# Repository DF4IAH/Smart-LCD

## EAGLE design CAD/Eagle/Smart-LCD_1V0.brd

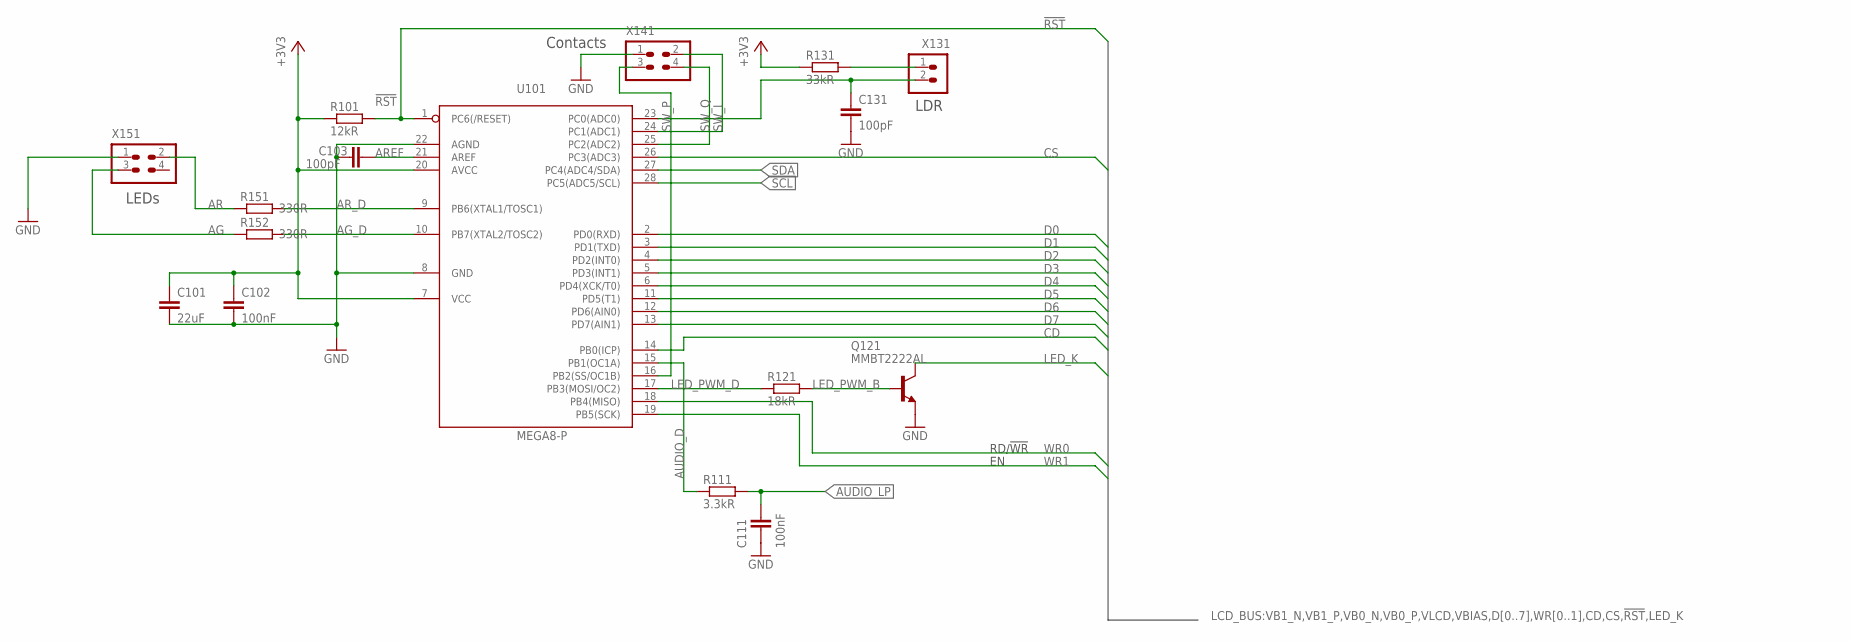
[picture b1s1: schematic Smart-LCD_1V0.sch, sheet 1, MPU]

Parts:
C101: 22uF; C0805
C102, C111: 100nF; C0805
C103, C131: 100pF; C0805
Q121: MMBT2222AL; SOT23
R101: 12kR; R0805
R111: 3.3kR; R0805
R121: 18kR; R0805
R131: 33kR; R0805
R151, R152: 330R; R0805
U101: MEGA8-P; DIL28-3
X131: LDR; 1X02
X141: Switches; 2X02
X151: LEDs; 2X02

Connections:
!RST: R101.2, U101.1 (PC6(/RESET)); also elsewhere on the board
+3V3: C101.1, C102.1, R101.1, R131.1, U101.7 (VCC), U101.20 (AVCC); also elsewhere on the board
AG: R152.1, X151.3
AG_D: R152.2, U101.10 (PB7(XTAL2/TOSC2))
AR: R151.1, X151.2
AREF: C103.2, U101.21 (AREF)
AR_D: R151.2, U101.9 (PB6(XTAL1/TOSC1))
AUDIO_D: R111.1, U101.15 (PB1(OC1A))
AUDIO_LP: C111.1, R111.2; also elsewhere on the board
CD: U101.14 (PB0(ICP)); also elsewhere on the board
CS: U101.26 (PC3(ADC3)); also elsewhere on the board
D0: U101.2 (PD0(RXD)); also elsewhere on the board
D1: U101.3 (PD1(TXD)); also elsewhere on the board
D2: U101.4 (PD2(INT0)); also elsewhere on the board
D3: U101.5 (PD3(INT1)); also elsewhere on the board
D4: U101.6 (PD4(XCK/T0)); also elsewhere on the board
D5: U101.11 (PD5(T1)); also elsewhere on the board
D6: U101.12 (PD6(AIN0)); also elsewhere on the board
D7: U101.13 (PD7(AIN1)); also elsewhere on the board
GND: C101.2, C102.2, C103.1, C111.2, C131.2, Q121.2 (E), U101.8 (GND), U101.22 (AGND), X141.1, X151.1; also elsewhere on the board
LDR: C131.1, U101.23 (PC0(ADC0)), X131.2
LDR_P: R131.2, X131.1
LED_K: Q121.3 (C); also elsewhere on the board
LED_PWM_B: Q121.1 (B), R121.2
LED_PWM_D: R121.1, U101.17 (PB3(MOSI/OC2))
SCL: U101.28 (PC5(ADC5/SCL)); also elsewhere on the board
SDA: U101.27 (PC4(ADC4/SDA)); also elsewhere on the board
SW_I: U101.24 (PC1(ADC1)), X141.2
SW_P: U101.16 (PB2(SS/OC1B)), X141.3
SW_Q: U101.25 (PC2(ADC2)), X141.4
WR0: U101.18 (PB4(MISO)); also elsewhere on the board
WR1: U101.19 (PB5(SCK)); also elsewhere on the board

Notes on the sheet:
LDR
Contacts
LEDs
RD/!WR

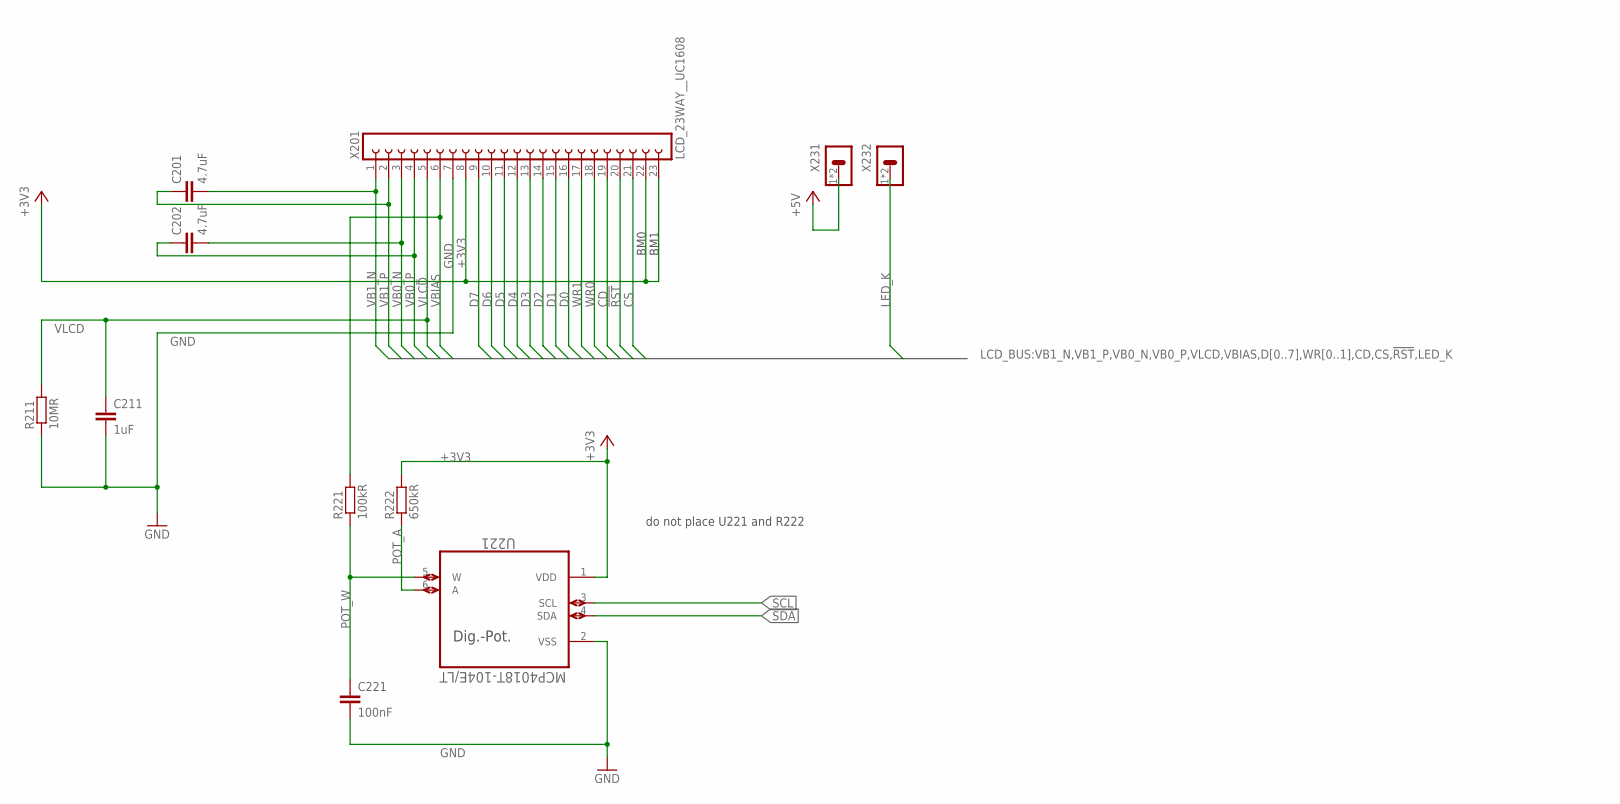
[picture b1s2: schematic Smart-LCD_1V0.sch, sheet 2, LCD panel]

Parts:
C201, C202: 4.7uF; C0805
C211: 1uF; C0805
C221: 100nF; C0805
R211: 10MR; R0805
R221: 100kR; R0805
R222: 650kR; R0805
U221: MCP4018T-104E/LT; SOT65P210X110-6N
X201: LCD_23WAY__UC1608; 23X01_1MM27__UC1608
X231: LED_A; P1-20X0.80
X232: LED_K; P1-20X0.80

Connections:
!RST: X201.20; also elsewhere on the board
+3V3: R222.2, U221.1 (VDD), X201.8, X201.22, X201.23; also elsewhere on the board
+5V: X231.1, X231.2; also elsewhere on the board
CD: X201.19; also elsewhere on the board
CS: X201.21; also elsewhere on the board
D0: X201.16; also elsewhere on the board
D1: X201.15; also elsewhere on the board
D2: X201.14; also elsewhere on the board
D3: X201.13; also elsewhere on the board
D4: X201.12; also elsewhere on the board
D5: X201.11; also elsewhere on the board
D6: X201.10; also elsewhere on the board
D7: X201.9; also elsewhere on the board
GND: C211.2, C221.2, R211.1, U221.2 (VSS), X201.7; also elsewhere on the board
LED_K: X232.1, X232.2; also elsewhere on the board
POT_A: R222.1, U221.6 (A)
POT_W: C221.1, R221.1, U221.5 (W)
SCL: U221.3 (SCL); also elsewhere on the board
SDA: U221.4 (SDA); also elsewhere on the board
VB0_N: C202.2, X201.3
VB0_P: C202.1, X201.4
VB1_N: C201.2, X201.1
VB1_P: C201.1, X201.2
VBIAS: R221.2, X201.6
VLCD: C211.1, R211.2, X201.5
WR0: X201.18; also elsewhere on the board
WR1: X201.17; also elsewhere on the board

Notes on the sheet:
Dig.-Pot.
BM1
BM0
do not place U221 and R222

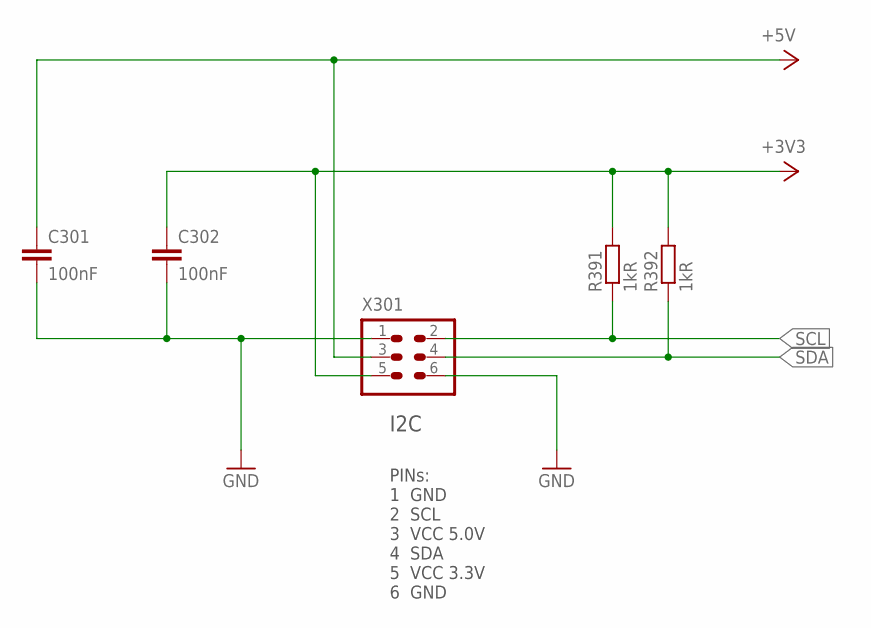
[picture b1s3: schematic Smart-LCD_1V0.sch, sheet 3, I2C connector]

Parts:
C301, C302: 100nF; C0805
R391, R392: 1kR; R0603
X301: I2C; 2X03

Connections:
+3V3: C302.1, R391.2, R392.2, X301.5; also elsewhere on the board
+5V: C301.1, X301.3; also elsewhere on the board
GND: C301.2, C302.2, X301.1, X301.6; also elsewhere on the board
SCL: R391.1, X301.2; also elsewhere on the board
SDA: R392.1, X301.4; also elsewhere on the board

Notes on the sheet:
I2C
PINs: 1 GND 2 SCL 3 VCC 5.0V 4 SDA 5 VCC 3.3V 6 GND

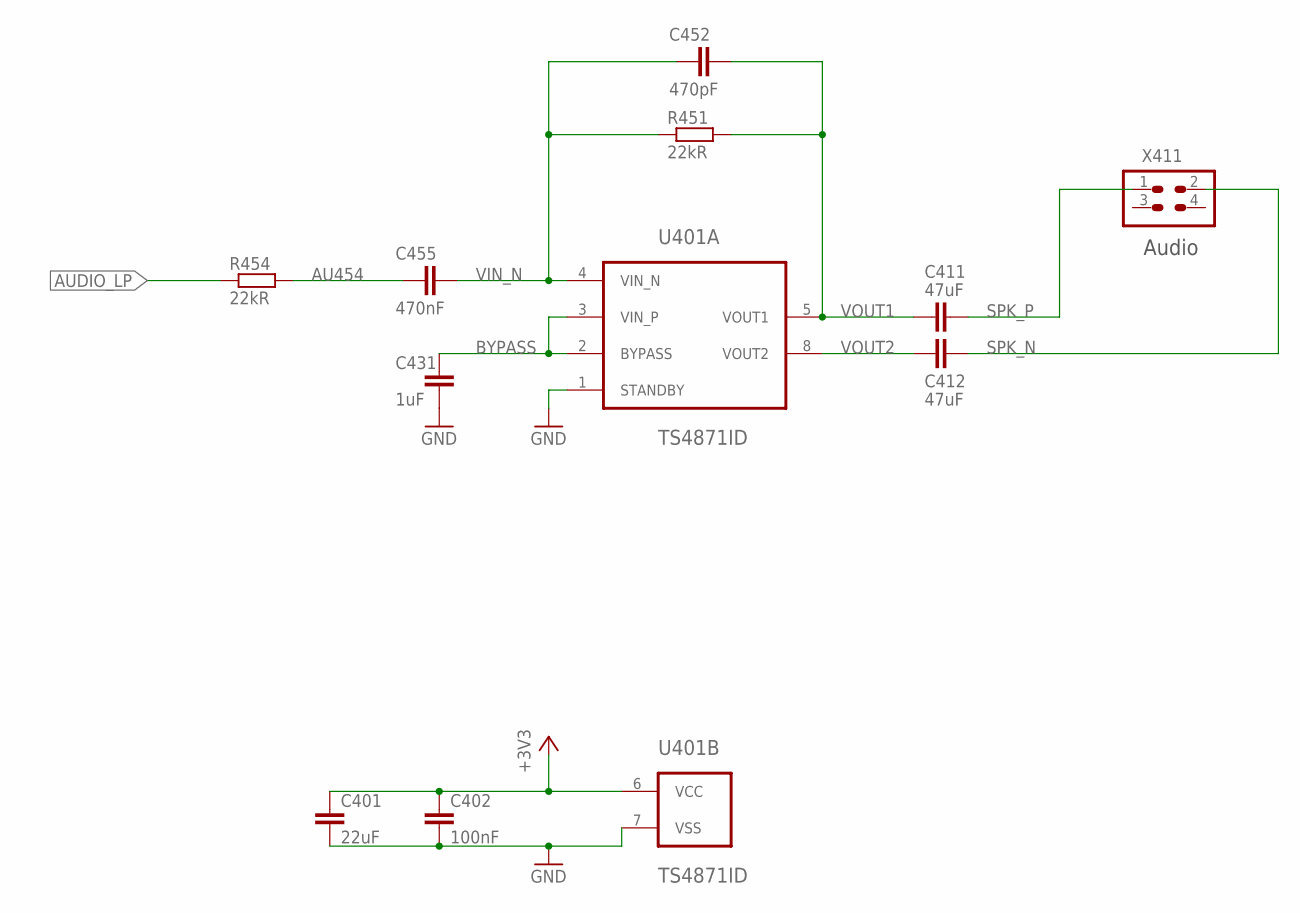
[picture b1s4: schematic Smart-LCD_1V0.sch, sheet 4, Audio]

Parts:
C401: 22uF; C0805
C402: 100nF; C0805
C411, C412: 47uF; C0805
C431: 1uF; C0805
C452: 470pF; C0805
C455: 470nF; C0805
R451, R454: 22kR; R0805
U401: TS4871ID; SO08
X411: Audio; 2X02

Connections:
+3V3: C401.1, C402.1, U401.6 (VCC); also elsewhere on the board
AU454: C455.1, R454.2
AUDIO_LP: R454.1; also elsewhere on the board
BYPASS: C431.1, U401.2 (BYPASS), U401.3 (VIN_P)
GND: C401.2, C402.2, C431.2, U401.1 (STANDBY), U401.7 (VSS); also elsewhere on the board
SPK_N: C412.2, X411.2
SPK_P: C411.2, X411.1
VIN_N: C452.1, C455.2, R451.1, U401.4 (VIN_N)
VOUT1: C411.1, C452.2, R451.2, U401.5 (VOUT1)
VOUT2: C412.1, U401.8 (VOUT2)

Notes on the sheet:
Audio

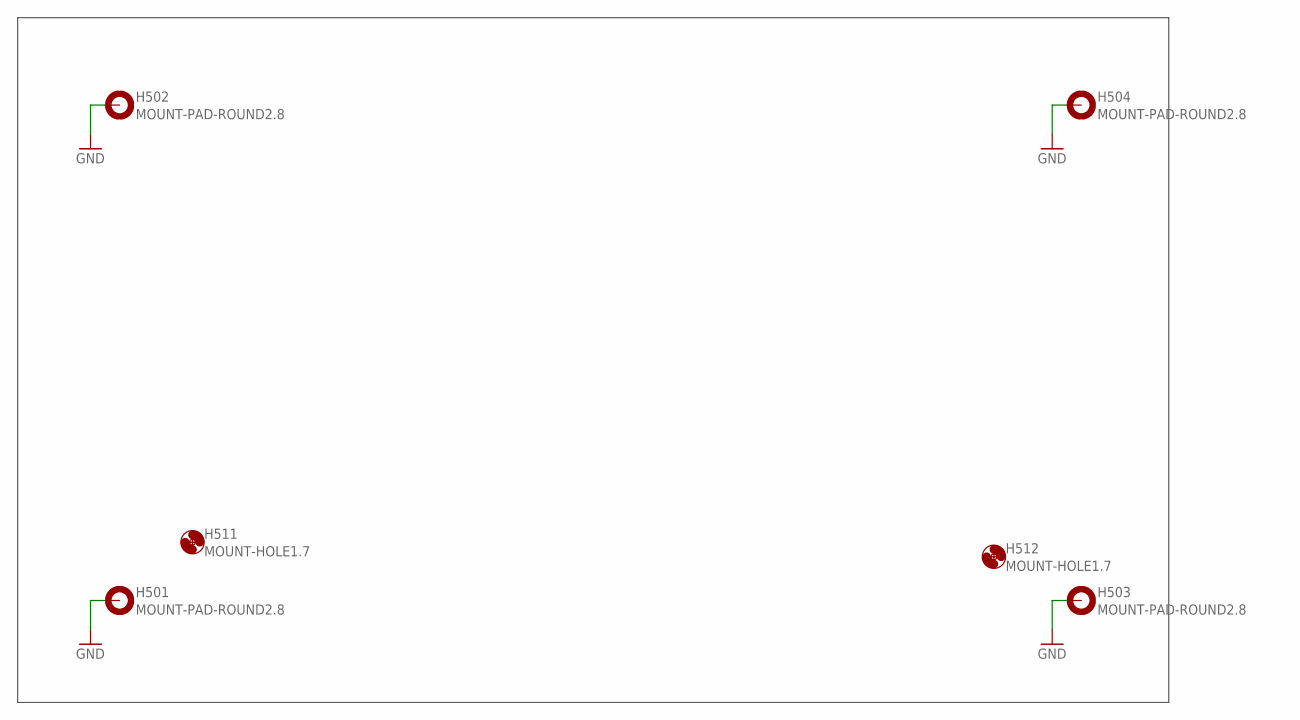
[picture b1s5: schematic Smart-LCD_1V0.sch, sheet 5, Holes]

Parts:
H501, H502, H503, H504: MOUNT-PAD-ROUND2.8; 2,8-PAD
H511, H512: MOUNT-HOLE1.7; 1,7

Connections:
GND: H501.B2,8, H502.B2,8, H503.B2,8, H504.B2,8; also elsewhere on the board

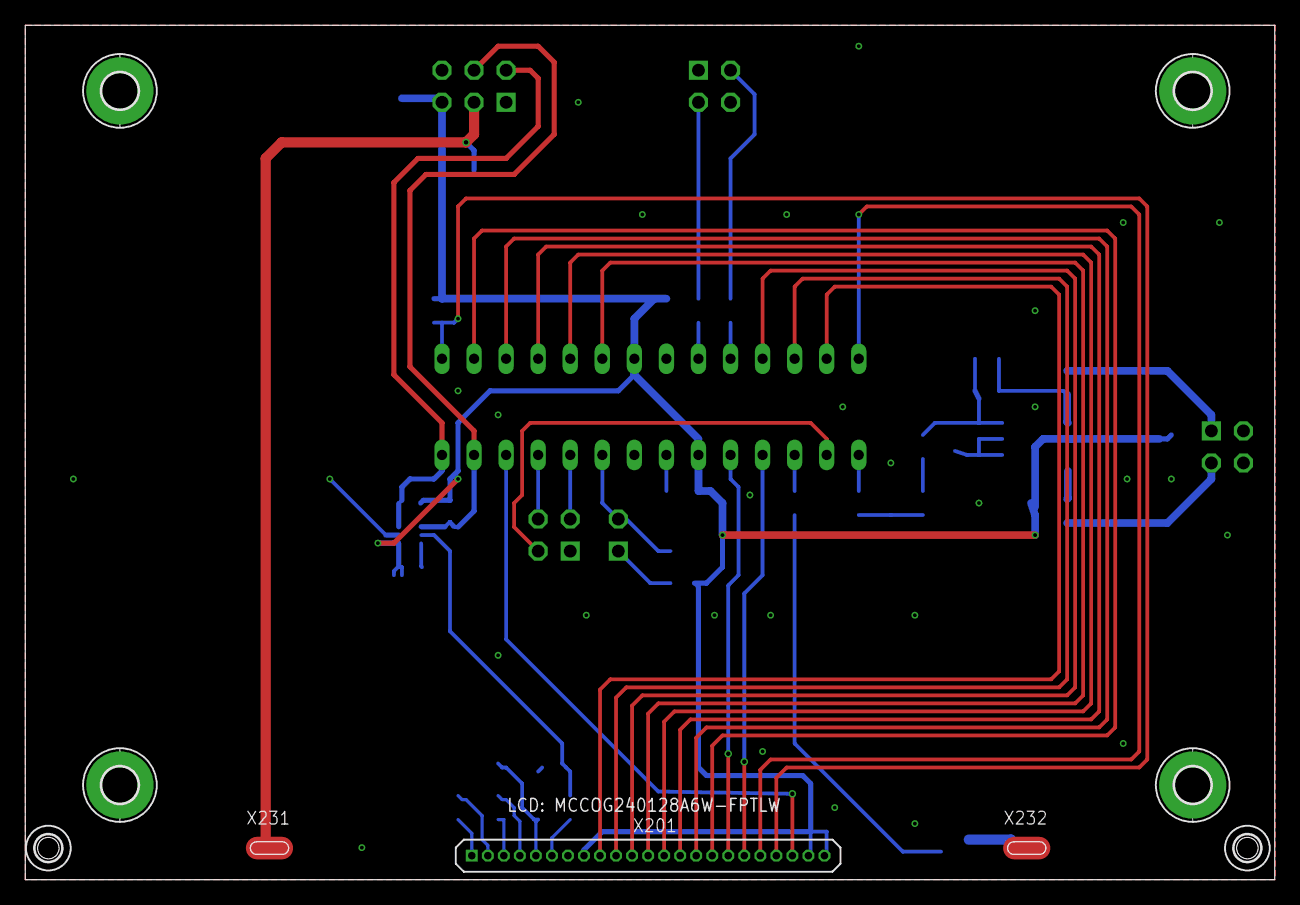
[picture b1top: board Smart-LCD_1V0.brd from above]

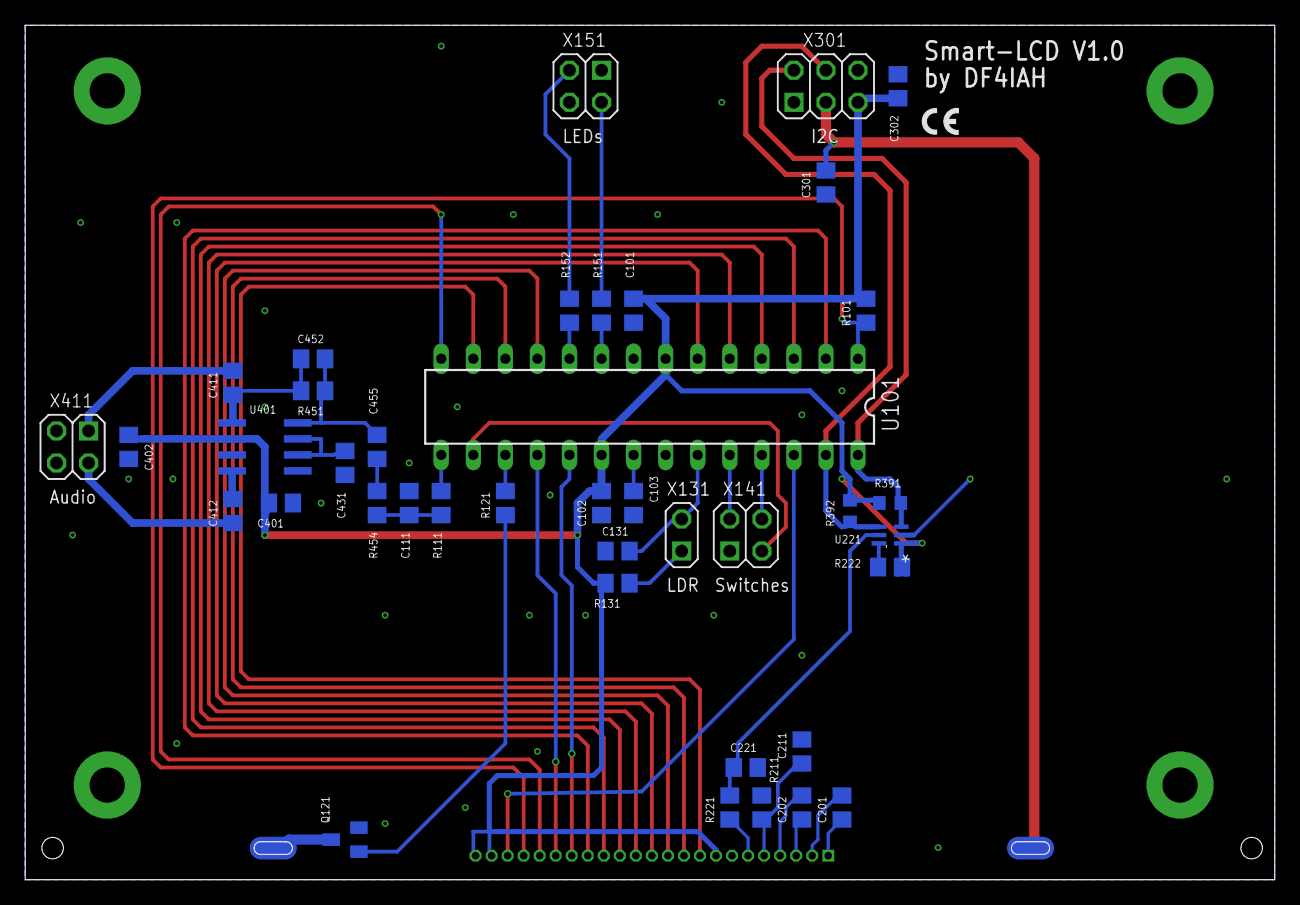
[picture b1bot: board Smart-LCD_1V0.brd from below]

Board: 2 copper layers, 99.0 x 67.7 mm, 49 parts (40 on the bottom side), 48 nets.

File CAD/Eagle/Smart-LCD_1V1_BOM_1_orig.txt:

Stückliste exportiert aus /Users/espero/Documents/eagle/Smart-LCD/Smart-LCD_1V1.sch am 30.05.17 14:22

Qty Value              Device             Package             Parts                              Description                            
1   100kR              R-EU_R0805         R0805               R221                               RESISTOR, European symbol              
6   100nF              C-EUC0805          C0805               C102, C111, C221, C301, C302, C402 CAPACITOR, European symbol             
2   100pF              C-EUC0805          C0805               C103, C131                         CAPACITOR, European symbol             
1   10MR               R-EU_R0805         R0805               R211                               RESISTOR, European symbol              
1   12kR               R-EU_R0805         R0805               R101                               RESISTOR, European symbol              
1   1MR                R-EU_R0805         R0805               R132                               RESISTOR, European symbol              
2   1kR                R-EU_R0805         R0805               R391, R392                         RESISTOR, European symbol              
2   1uF                C-EUC0805          C0805               C211, C431                         CAPACITOR, European symbol             
2   22kR               R-EU_R0805         R0805               R451, R454                         RESISTOR, European symbol              
2   22uF               C-EUC0805          C0805               C101, C401                         CAPACITOR, European symbol             
1   27R                R-EU_R0805         R0805               R131                               RESISTOR, European symbol              
1   3.3kR              R-EU_R0805         R0805               R111                               RESISTOR, European symbol              
2   330R               R-EU_R0805         R0805               R151, R152                         RESISTOR, European symbol              
1   4.7kR              R-EU_R0805         R0805               R121                               RESISTOR, European symbol              
2   4.7uF              C-EUC0805          C0805               C201, C202                         CAPACITOR, European symbol             
1   470nF              C-EUC0805          C0805               C455                               CAPACITOR, European symbol             
1   470pF              C-EUC0805          C0805               C452                               CAPACITOR, European symbol             
2   47uF               C-EUC0805          C0805               C411, C412                         CAPACITOR, European symbol             
1   650kR              R-EU_R0805         R0805               R222                               RESISTOR, European symbol              
1   Audio              HEADER-2X2         2X02                X411                               Header 2X2 2.54mm                      
1   BZX84-C2V4         BAS70-04           SOT23               D131                               Silicon Schottky Diodes                
4   FIDUCIAL_MARK_1MM  FIDUCIAL_MARK_1MM  FIDUCIAL_MARK_1MM   FM501, FM502, FM503, FM504         Fiducial Mark                          
1   I2C                HEADER-2X3         2X03                X301                               Header 2X3 2.54mm                      
1   LCD_23WAY__UC1608  LCD_23WAY__UC1608  23X01_1MM27__UC1608 X201                               Gfx-LCD UC1608 socket                  
1   LDR                HEADER-1X2         1X02                X131                               Header 1X2 2.54mm                      
1   LED_A              CON_1X             P1-20X0.80          X231                               THT contact 2mm x 0.80mm               
1   LED_K              CON_1X             P1-20X0.80          X232                               THT contact 2mm x 0.80mm               
1   LEDs               HEADER-2X2         2X02                X151                               Header 2X2 2.54mm                      
1   MCP4018T-104E/LT   MCP4018T-104E/LT   SOT65P210X110-6N    U221                               Digital POT                            
1   MEGA8-P            MEGA8-P            DIL28-3             U101                               MICROCONTROLLER                        
1   MMBT2222AL         MMBT2222AL         SOT23               Q121                               MMBT2222L, MMBT2222AL, SMMBT2222AL     
2   MOUNT-HOLE1.7      MOUNT-HOLE1.7      1,7                 H511, H512                         MOUNTING HOLE with drill center marker 
4   MOUNT-PAD-ROUND2.8 MOUNT-PAD-ROUND2.8 2,8-PAD             H501, H502, H503, H504             MOUNTING PAD, round                    
1   Switches           HEADER-2X2         2X02                X141                               Header 2X2 2.54mm                      
1   TS4871ID           TS4871ID           SO08                U401                               STMICROELECTRONICS  TS4871ID

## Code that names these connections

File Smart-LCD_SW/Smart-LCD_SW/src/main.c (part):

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	 * most critical pins are handled first.
	 */

	PORTB = 0b00010100;												// PB0: LCD-CD out-LO, PB1: AUDIO out (OC1A), PB2: SW_P in-PU, PB3: LCDBL out-AF-OC2A,
	DDRB  = 0b11111011;												// PB4: LCD-R/!W out-HI, PB5: LCD-EN out-LO, PB6: LEDRD out-LO, LEDGN out-LO

	PORTC = 0b01111110;												// PC0: LDR-ADC in-NoPU, PC1: SW_I in-PU, PC2: SW_Q in-PU, PC3: LCD-CS out-HI
	DDRC  = 0b00001000;												// PC4: I2C-SDA in-PU-AF-TWI, PC5: I2C-SCL in-PU-AF-TWI, PC6: RESET in-PU, PC7: -

	PORTD = 0xff;													// PD0..PD7: LCD-D0..LCD-D7 in-PU
	DDRD  = 0x00;

	// Analog input: Digital Disable Register
	DIDR0 = 0b00000001;												// PC0: LDR-ADC
}

static void s_tc_init(void)
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
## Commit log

2017-01-24 CAD, Docs - initial set-up
2017-01-24 SW - initial set-up
2017-02-03 CAD/Docs - initial set-up for new design
2017-02-04 CAD - first layout worked on
2017-02-04 Docs - BJT added
2017-02-04 Docs - ATmega328P added
2017-02-05 CAD - routed, but audio amplifier still TODO
2017-02-06 CAD - audio amplifier added, but CPU must be placed on the solder side
2017-02-06 CAD - CPU placed on the solder side
2017-02-07 CAD - minor corrections and PCB V1.0 ordering done
2017-02-08 SW - initial set-up with AVR-studio
2017-02-08 SW - ASF included
2017-02-08 SW - top-level main.c removed and ASF minimal code compiled
2017-02-08 SW - all needed ASF services and drivers added
2017-02-08 SW - I/O wires connected
2017-02-08 SW - some tests with the vector table done
2017-02-10 SW - TC0/1/2 init done
2017-02-11 SW - ADC init done, ISR: ADC done
2017-02-12 SW - sleep added, some more init and disable code added
2017-02-12 SW - SEI and CLI changed
2017-02-13 SW - ISR routines moved to isr.c|h module
2017-02-13 SW - TWI init added
2017-02-13 SW - TWI shutdown added
2017-02-13 SW - TWI state-machine added
2017-02-21 SW - TWI state-machine completed, TX double buffering added
2017-02-23 SW - LCD module added, additional sources for gfx_mono handling included
2017-02-23 SW - gfx_mono - hooks for LCD UC1608 added
2017-02-23 SW - gfx_mono - communication with UC1608 LCD implemented
2017-02-26 SW - display attached to new arrived PCB, some changes done at the LCD communication section
2017-02-26 SW - most of the display works, still searching for timer bug
2017-02-27 SW - timers are running, ADC ISR only one time called
2017-02-27 SW - ADC temperature working
2017-02-27 SW - test code for PWM channels of audio out and LCD backlight added
2017-02-27 CAD - changed value - C111 22nF --> 100 nF
2017-02-27 SW - uint8_t lcd_bus_read_ram(void) optimized and OK
2017-02-27 SW - void lcd_bus_write_ram(uint8_t data) optimized and OK
2017-02-27 SW - void lcd_bus_write_cmd(uint8_t cmd) optimized and OK
2017-02-27 SW - uint8_t lcd_bus_read_status(void) optimized and OK
2017-02-27 SW - demo animation complete
2017-02-28 SW - LDR backlight ready, LCD demo enhanced
2017-02-28 CAD - new version V1.1 - missing resistor for LDR added, missing header pin number 1 marking added
2017-02-28 CAD - four fiducials added
2017-03-03 SW - TWI interface - slave receive mode implemented and some tests done
2017-03-04 SW - TWI interface - some debugging around STOP/START that triggers a problem in the TWI state-machine
2017-03-04 SW - sleep mode enabled - TWI: no more debugging with 10MHz-Ref-Osc possible due to error there
2017-03-04 CAD - I2C pull-ups changed to 1kR
2017-03-05 CAD - wire sizes of less than 0.3048 changed to 0.3048mm
2017-03-05 SW - branching works
2017-03-05 CAD - branching works
2017-03-05 Docs - new branch added
2017-03-05 master - branching works
2017-03-26 HW_V1.1 - LCD backlight basis resistor chnaged to 4.7k ohms
2017-03-27 SW - backlight control added - some more to do
2017-03-29 SW - I2C version request answered
2017-03-30 SW - first I2C version command OK, second one implemented
2017-03-31 SW - backlight illumination for V1.1 now OK
2017-03-31 SW - renaming from LDR to PD (photo diode) of the V1.1 design
2017-03-31 SW - missing show_clk_state added
2017-04-02 SW - displaying all 10MHz-Ref.-Osc. parameters at I2C address 0x22
2017-04-02 SW - more TWI fixes done
2017-04-02 SW - TWI data of latitude/longitude reworked
2017-04-03 SW - some more TWI issues fixed
2017-04-04 SW - LCD fine tuning
2017-04-07 SW - TWI message processing decoupled from data presentation
2017-04-07 SW - repaint changed values only
2017-04-07 SW - some more graphic issues
2017-04-08 SW - TWI - ISR functions are constantly in disabled interrupt context
2017-04-08 SW - display PWM value, fractional part fixed
2017-04-08 HW_V1.1 - photo diode - resistor change from 100k to 1MR
2017-04-08 SW - Duo-LED and audio interface activated
2017-04-09 SW - acoustic phase tracker added
2017-04-10 SW - interrupt optimizations
2017-04-14 SW - phaseVolt display added
2017-04-15 SW - turn PhaseOfs indicator in opposite direction
2017-04-15 SW - degree sign added
2017-04-15 SW - PWM value presentation fixed
2017-04-15 SW - phase offset sound pitch deviation reversed
2017-04-16 SW - PWD data display trimmed
2017-04-16 SW - receiving and presentation of height information in meters.decimeters
2017-04-16 SW - message length of meters.decimeters fixed
2017-05-13 SW - PhaseOfs left/right now max 45deg instead of 180deg
2017-05-14 SW - PhaseOfs left/right now max 45deg instead of 180deg (2)
2017-05-14 SW - PhaseOfs *4 for audio pitch calculation
2017-05-30 HW_V1.1 - BOM added
2017-05-30 HW_V1.1 - BOM removed again
2017-05-30 DOCS - BOM added
2017-05-30 HW_V1.0 - screenshots of schematic and board added
2017-05-30 HW_V1.1 - I2C poti removed
2017-05-30 master - hiding historic V1.0 files
2017-05-30 DOCS - BOM added (2)
2017-05-30 SW - info about fuse settings added
2017-05-31 SW - LCD contrast voltage setting by Switch-I/-Q input for increase and decrease of voltage. Push button for writing setting into the EEPROM.
2017-06-10 SW - update to version ASF 3.34.1
2017-06-10 SW - Smart-LCD version now V1.1
2017-06-10 SW - multi mode design for the Smart-LCD command set created
2017-06-10 SW - minor tweaks done
2017-06-12 SW - work of the day: TWI / LCD indirect communication for different context introduced
2017-06-13 SW - animated loop - bad recursive call removed
2017-06-13 SW - s_task() is not static any more, renamed to task()
2017-06-17 SW - some data index positions fixed
2017-06-18 SW - communication now OK
2017-06-18 SW - remove trailing spaces
2017-06-20 HW_V1.1 - screenshots added
2017-06-20 HW_V1.1 - suggestions of Hans, DK1NB added
2017-06-20 SW - plotting text issue done
2017-06-22 SW - one-byte read cache added
2017-06-22 SW - caching code a little bit optimized
2017-06-22 SW - automatic mode selection added for old 10 MHz-Ref-Osc firmware not switching mode itself
2017-06-22 SW - automatic mode selection removed again
2017-06-25 HW_V1.1 - LCD backlight - 1 ohms added to the NPN's emitter
2017-06-25 HW_V1.1 - df4iah_connector.lbr combined for Smart-LCD and FindMeSAT
2017-06-25 HW_V1.1 - df4iah_connector.lbr combined for Smart-LCD and FindMeSAT (2)
2017-06-25 SW - much code replacement with ISR related functions
2017-06-28 SW - display area organized for demo mode, rotary switch decoder implemented
2017-07-20 SW - command set enhanced, pixel type argument added for line/rect/circle
2017-07-20 SW - version updated
2017-07-20 SW - command set enhanced, pixel type argument added for line/rect/circle (2)
2017-07-25 SW - TWI - new commands for backlight, LEDs, rotary encoder and more - untested code
2017-07-27 SW - TWI - contrast settings fixed
2017-08-05 SW - TWI - reset command added, cls command has new address
2017-08-07 SW - backlight level=0 now turns off completly
2017-08-23 MIT LICENSE file added
2017-09-18 SW - Sound changed from PWM to digital output - removes 16 kHz tone
2018-03-14 HW_V1.0 - do not place I2C poti
